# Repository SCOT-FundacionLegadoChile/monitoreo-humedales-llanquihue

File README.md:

# Monitoreo de Humedales en Llanquihue
Repositorio del desarrollo de equipos tecnológicos de monitoreo para humedales en llanquihue.

## Arduino & inAir9 (LoRa)

### Librería RadioHead
Se utiliza la librería RadioHead.h para la comunicación por LoRa (https://github.com/PaulStoffregen/RadioHead).

IMPORTANTE: Se agregaron métodos por lo que es necesario instalar esta versión de la librería.

Instalación:
1. Mover carpeta ./RadioHead/ a carpeta ~/Arduino/libraries/
2. Verificar que librería está disponible en IDE Arduino
3. Ser feliz y salir a comer algo.

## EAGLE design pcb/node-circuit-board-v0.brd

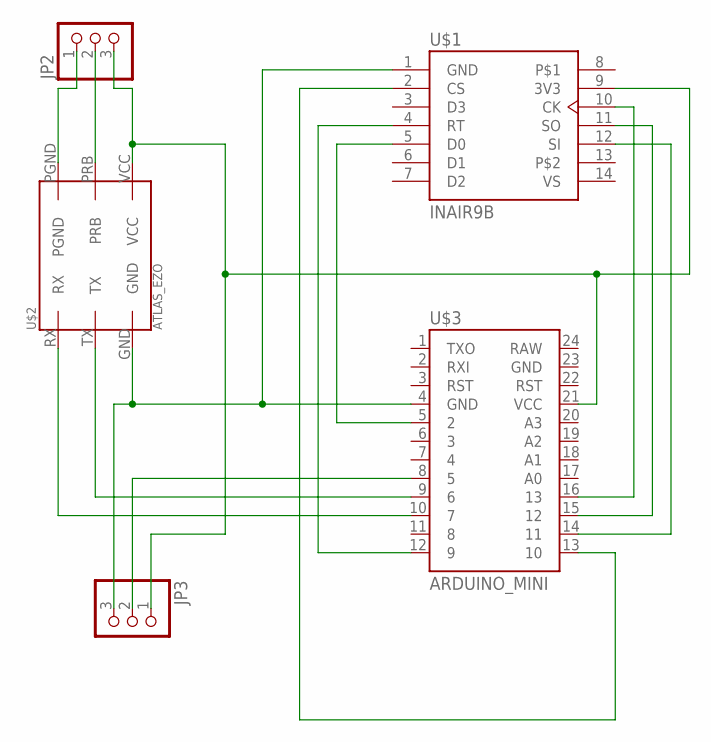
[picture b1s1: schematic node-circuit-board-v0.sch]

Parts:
JP2, JP3: PINHD-1X3CB; 1X03-CLEANBIG
U$1: INAIR9B; INAIR
U$2: ATLAS_EZO
U$3: ARDUINO_MINI

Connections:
unnamed: U$1.2 (CS), U$3.13 (10)
unnamed: U$1.4 (RT), U$3.12 (9)
unnamed: U$1.5 (D0), U$3.5 (2)
unnamed: U$1.10 (CK), U$3.16 (13)
unnamed: U$1.11 (SO), U$3.15 (12)
unnamed: U$1.12 (SI), U$3.14 (11)
unnamed: JP3.3, U$1.1 (GND), U$2.GND, U$3.4 (GND)
unnamed: U$2.TX, U$3.9 (6)
unnamed: U$2.RX, U$3.10 (7)
unnamed: JP2.1, U$2.PGND
unnamed: JP2.3, JP3.1, U$1.9 (3V3), U$2.VCC, U$3.21 (VCC)
unnamed: JP2.2, U$2.PRB
unnamed: JP3.2, U$3.8 (5)

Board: 2 copper layers, 5 parts (0 on the bottom side), 13 nets, no tracks yet.

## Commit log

2017-12-04 First commit. Tested in llanquihue Nov 2017.
2017-12-04 Credencial and keys know in separate creds.py file.
2017-12-05 Iniciando como servicio. Datos de prueba
2017-12-05 Pruebas Cobertura Llanquihue Nov 2017
2017-12-07 avanzando en gw
2017-12-07 Ported arduino_gw to PlatformIO
2017-12-07 New RH_RF95 configure lora params function
2017-12-07 .ino file to .cpp in platformio
2017-12-07 ported tx node arduino to platformio
2017-12-07 ignore travis.yml platformio files
2017-12-07 include libraries
2017-12-08 Pruebas LoRa con madera
2017-12-31 new docs
2018-03-22 muchas cosas de las que no segui track
2018-03-23 Datos de cobertura en llanquihue con nodo dentro de totem
2018-04-02 Listo para programar! :D
2018-04-02 Puerto serial liberado y traspasado a pines 3 y 4
2018-04-18 pcb + version 3 programa nodo (- energia)
2018-04-21 nuevas librerias y leves mejorasde codigo
2018-04-22 gw guarda mensaje completo
2018-04-22 programa v0 gw
2018-04-22 programa otro
2018-04-22 programa otroo
2018-04-24 GW puede hacer update a traves de git
2018-04-24 GW puede hacer update a traves de git 2
2018-04-24 GW puede hacer update a traves de git 3
2018-04-24 GW puede hacer update a traves de git 4
2018-05-12 new gw firmware
2018-05-12 nuevo firmware gw
2018-10-28 no se que estoy haciendo, solo actualizando

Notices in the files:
parts and their libraries:
SparkFun-Retired: Licensing: Creative Commons ShareAlike 4.0 International - https://creativecommons.org/licenses/by-sa/4.0
